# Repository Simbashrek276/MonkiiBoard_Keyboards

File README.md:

# MonkiiBoard Keyboards

Hi! This is the home for the MonkiiBoard keyboards, an open little family of boards you can build, flash and print yourself. There are five of them so far, and each one lives in its own folder with the Arduino code, a 3D printable case and a readme that walks you through it. Remember, for every build (aside from MonkiiPad16 and MonkiiBoard58), there will be 2 build pathways you can take, which are either handwiring or PCB-based builds. For starters, I would recommend choosing the handwiring option for certain keyboard builds, as it would make it much more easier to debug and fix using a multimeter and other tools as well!

## The boards

### MonkiiBoard58
MonkiiBoard58 is the newest and the most ambitious build here! This board packed fifty eight keys in a five by twelve ortholinear grid with a rotary encoder on the left, a ESP23 S3 WROOM U1 (Surface mounted component, not through hole) and no cable to the host at all since it runs wireless off a LiPo battery over Bluetooth (well of course we still have to charge the battery by pluggin the USB_C Receptacle in).

Up to this point, this board only exists as a PCB, no hand wired version, since it carries its own LiPo charger, voltage regulator and a MOSFET power gate for the OLED right alongside the switch matrix. The schematic and layout are finished and the gerbers are ready, but the boards have not gone off to a manufacturer yet, so this is the one board here that has not actually been built in real life.

### MonkiiBoard39
MonkiiBoard39 is MonkiiBoard's second build. THis keyboard has thirty nine keys in a tidy ortholinear 40 percent layout, with sticky modifiers on the bottom row and a Windows key that pops the start menu on a double tap.

MonkiiBoard39 has a PCB now too, no diodes on this one since the sticky modifiers never need more than one key held down at a time. The schematic below shows all thirty nine switches wired straight into the matrix, with the Pro Micro footprint sitting right in the middle of the board.

### MonkiiPad20
MonkiiPad20 is our first keyboard with a OLED screen implemented. This macropad is a a twenty key macropad with an OLED screen, two switchable layers and a set of animated robot eyes that appear when you stop using it for a while (approximately 6 - 8 seconds). It is also the only board here that uses diodes (so far).

For the MonkiiPad20, we've also made our earliest PCB version 1 for this very macropad (if you choose to go the PCB path instead of the handwiring path)! The image below taken is the PCB, where you can see a silkscreen of our logo, MonkiiBoard, on the front layer.

### MonkiiBoard3x3
MonkiiPad3x3 is the first keyboard that we made!! It's a nine key pad that works as a plain number pad until you hold one key (the key "1") to flip it into a macro mode full of arrows and editing shortcuts.

MonkiiPad3x3 got the same treatment, a little PCB with all nine switches and the Pro Micro packed onto one small board, diode free just like MonkiiBoard39.

### MonkiiPad16
MonkiiPad16 is our upgraded macropad, with a knob! This macropad has 16 keys and a rotary encoder, so instead of a second board or a held down FN key you just SPIN the knob to pick a layer, a numpad by default and a page of editing shortcuts one turn away.

## What is in each folder

Every folder is laid out the same way. There is a firmware folder with the Arduino sketch you flash onto the board, a case folder with the print ready STL plates you can drop straight into a slicer, and a readme that covers the wiring, the layout and whatever that particular board likes to do. MonkiiBoard58 is the exception for now, since it has not been built yet its folder only holds the PCB.

## Hand wired or PCB

We designed every board here except MonkiiPad16 and MonkiiBoard58 to be built either hand wired or on its PCB, same firmware and the same layout either way. Hand wiring asks a bit more of you on the materials side, thin gauge wire to run the rows and columns, insulating tape to keep the joints from touching each other, and a steadier hand while you solder everything point to point. The PCB skips all of that since the rows and columns are already routed for you, so it comes down to seating the parts and soldering them to the footprint.

| Needed for | Hand wired | PCB |
| --- | --- | --- |
| Soldering station | Yes | Yes |
| Multimeter | Yes | Yes |
| Solder | Yes | Yes |
| Switches | Yes | Yes |
| Controller board | Yes | Yes |
| Thin wire | Yes | No |
| Insulating tape | Yes | No |
| The PCB itself | No | Yes |

MonkiiPad20 and MonkiiBoard58 are the only boards that need diodes, both 1N4148s, one for every switch. MonkiiBoard39 and MonkiiPad3x3 skip them completely on both their hand wired and PCB builds, and we code the MCUs to enable toggling keys for combinations like Ctrl+C and Ctrl+V instead of holding Ctrl and then press the other button.

## A word on diodes

MonkiiPad20 and MonkiiBoard58 both have a diode sitting under each switch, which is what gives them a clean matrix and proper rollover. The other two boards skip the diodes to keep the build simple and cheap, so they are at their happiest when you press one or two keys at a time. Worth knowing before you start soldering, or before you order parts if MonkiiBoard58 is the one you are building.

## The PCBs at a glance

Four of the five boards now have a PCB option, all designed in KiCad as two layer boards. Here is how they compare.

| Board | Keys | Matrix | Diodes | Controller | Board size |
| --- | --- | --- | --- | --- | --- |
| MonkiiBoard39 | 39 | 4 by 10 | No | Pro Micro (ATmega32U4) | 195 by 80 mm |
| MonkiiPad20 | 20 | 4 by 6 | Yes | RP2040-Zero | 120 by 86 mm |
| MonkiiPad3x3 | 9 | 3 by 3 | No | Pro Micro (ATmega32U4) | 57 by 57 mm |
| MonkiiBoard58 | 58 | 5 by 12 | Yes | ESP32-S3-WROOM-1 N16R8 | 235.45 by 122.95 mm |

MonkiiBoard58 is also the only one of the four running wireless, with its own LiPo charging and voltage regulation on board, and the only one still waiting to actually be manufactured.

Each PCB folder has the full design story, the schematic, the gerbers to get one made, and the raw KiCad project if you want to tune or reroute your own version.

## Getting started

Pick the board you want, open its folder and read through its readme. Wire the matrix to match the pins listed there, flash the sketch from the Arduino IDE, print the plates from the case folder, and you have yourself a keyboard.

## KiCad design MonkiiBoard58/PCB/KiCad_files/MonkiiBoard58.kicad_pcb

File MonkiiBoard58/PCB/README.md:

# MonkiiBoard58 PCB

MonkiiBoard58 is the first board in the family that only exists as a PCB. There is no hand wired version of this one. Fifty eight switches, a rotary encoder and an OLED screen all packed onto one board, running wireless off a LiPo battery instead of a USB cable to the host.

## The layout

Fifty eight keys sit in a five row by twelve column ortholinear grid, sixty switch positions in total with two given up in the middle for the OLED window. An EC11 rotary encoder lives on the left side and a USB C receptacle sits in the top right corner for charging.

## How I designed it

I drew the matrix first, fifty eight switches each with their own 1N4148 diode, then moved on to the ESP32 S3 module, the OLED header, the encoder and the whole power section afterward.

The power side got its own sheet since there was too much going on to squeeze in next to the matrix. Battery connector, power switch, the AMS1117 regulator and its capacitors all sit together here.

## Laying it out

The first pass at routing did not have a single mounting hole anywhere on the board, which would have left no way to actually screw it into a case later. Version two added four of them, one in each corner.

## Placing and wiring the parts

Before anything got soldered I laid every part out on the bench to check the footprints against the real components first.

## The power system

This is the part that sets MonkiiBoard58 apart from the rest of the family. USB C brings in five volts, the TP4056 uses that to charge the LiPo battery, and everything downstream of the power switch runs off the AMS1117 regulator at a steady 3.3 volts.

| Stage | Part | Job |
| --- | --- | --- |
| Charging | TP4056 | Charges the LiPo off USB C, current set by a 1.2 kilo ohm PROG resistor, up to one amp |
| Regulation | AMS1117 3.3 | Takes the battery voltage and holds a steady 3.3 volt rail for everything else |
| OLED gating | AO3401A | P channel MOSFET that cuts power to the OLED completely when the ESP32 S3 pulls the gate high |
| Battery sensing | Resistor divider | 1 megaohm and 806 kiloohm divider scaling the 4.2 volt max battery voltage down into the ADC range |

The OLED gate is the part I am proudest of. Instead of just dimming the screen in software, the ESP32 S3 can cut its power rail entirely after thirty seconds of no key presses, so there is zero standby draw from the display while the board sits idle.

## The switches

All fifty eight switches sit in a five row by twelve column matrix, and unlike MonkiiBoard39 or MonkiiPad3x3 this one does use a diode per switch, a 1N4148 with the cathode facing the row line. With sixty positions on a wireless board meant for real typing, full rollover mattered enough to spend the extra part on every switch.

## The pinout

| Function | ESP32 S3 GPIO |
| --- | --- |
| Row 0 | GPIO4 |
| Row 1 | GPIO5 |
| Row 2 | GPIO6 |
| Row 3 | GPIO7 |
| Row 4 | GPIO8 |
| Col 0 | GPIO9 |
| Col 1 | GPIO10 |
| Col 2 | GPIO11 |
| Col 3 | GPIO12 |
| Col 4 | GPIO13 |
| Col 5 | GPIO14 |
| Col 6 | GPIO15 |
| Col 7 | GPIO16 |
| Col 8 | GPIO17 |
| Col 9 | GPIO18 |
| Col 10 | GPIO21 |
| Col 11 | GPIO38 |
| OLED SDA | GPIO1 |
| OLED SCL | GPIO2 |
| OLED power gate | GPIO39 |
| Encoder A | GPIO40 |
| Encoder B | GPIO41 |
| Encoder switch | GPIO42 |
| Battery ADC | GPIO3 |

## The controller

An ESP32 S3 WROOM 1 N16R8 sits at the top center of the board, antenna facing out toward the edge with a keep out zone underneath it so nothing on any layer sits under or around the antenna. The S3 has a native USB PHY, so the USB C lines wire straight into it with no separate USB to serial chip needed, and it talks Bluetooth 5 for the wireless side once the firmware is flashed.

## What the board is

| Spec | Value |
| --- | --- |
| Layers | 2 |
| Thickness | 1.6 mm |
| Size | 235.45 by 122.95 mm |
| Finish | None |

## Downloading the files

`MonkiiBoard58_PCB.zip` in this folder has the copper, mask, paste and silkscreen layers for both sides along with the edge cuts and the job file. There is no drill file in there yet, so pull that from the KiCad project in `KiCad_files` and add it before sending this off to a fab house.

## Tuning your own PCB

If you want to design or tune your own version of this board, the raw KiCad project sits in `KiCad_files` right next to the gerbers. Download those three files, open the `.kicad_pro` in KiCad, and you get the schematic and the board exactly as I left them. Edit the schematic, move footprints, reroute traces, whatever your build actually needs, then export your own gerbers when you are happy with it.

## Where things stand right now

This one is still ahead of the rest of the pack in age but behind everyone else in progress. The schematic and layout are done and the gerbers are ready, but I have not sent the boards off to a manufacturer yet, so nothing has actually been built or tested on real hardware. Firmware and a case are next once boards are in hand. Like every other board here it is fully open source, so the KiCad project and every file in this folder are free to build, copy or change however you like.

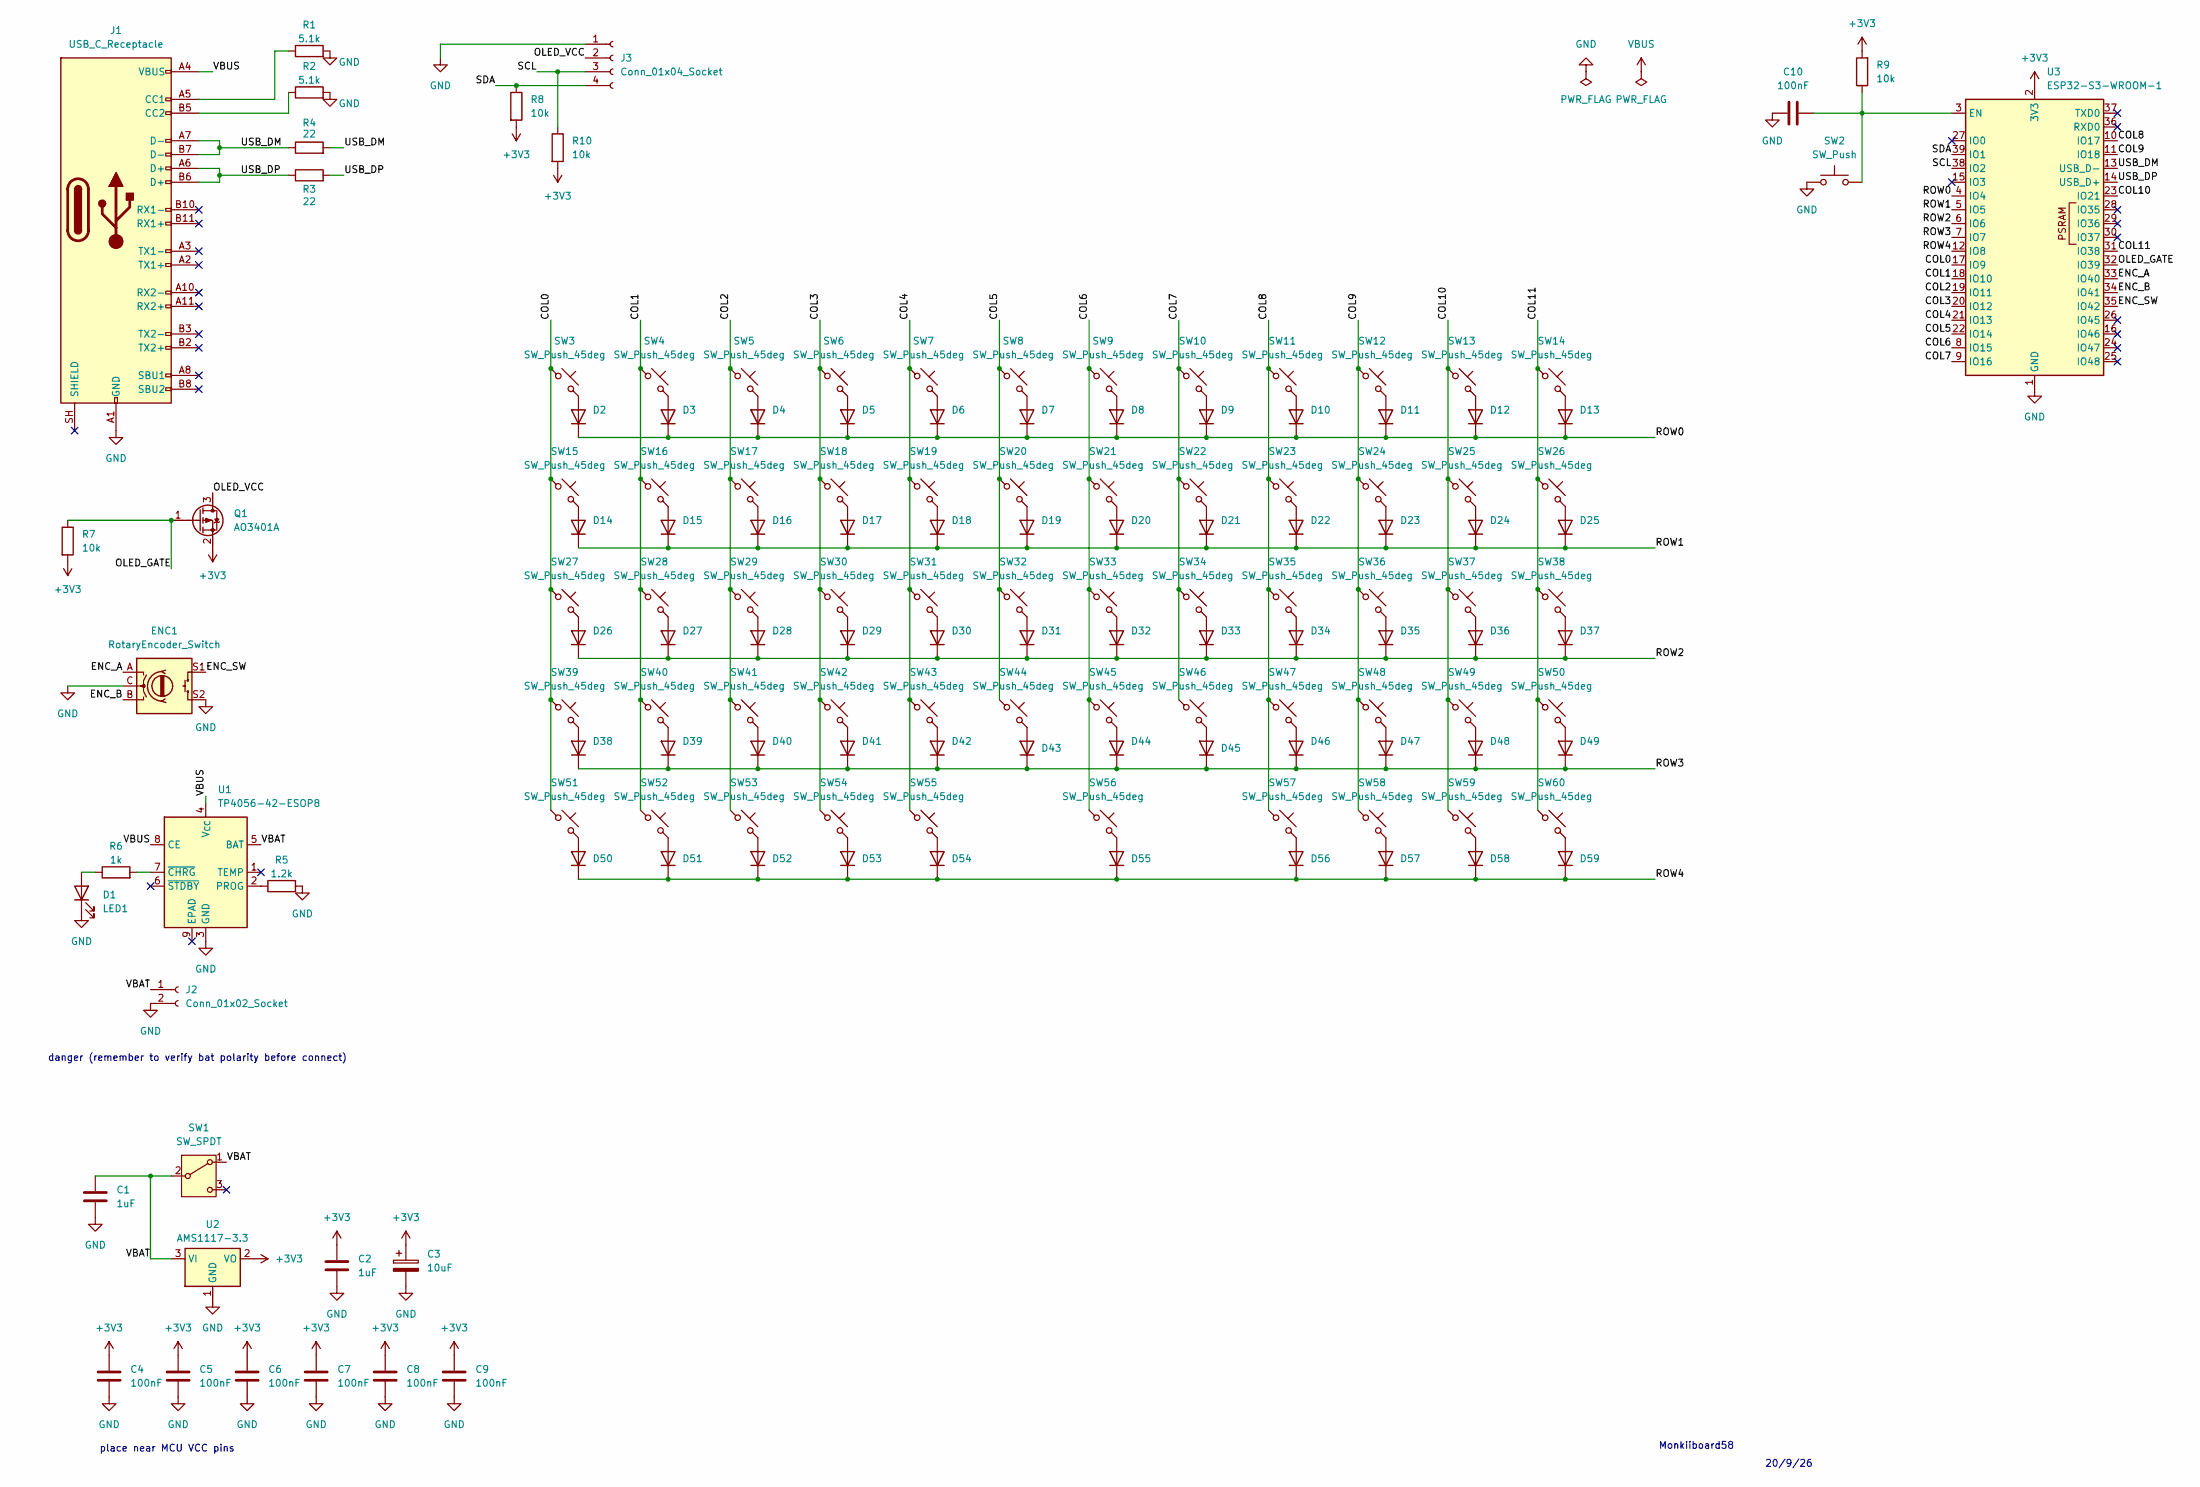
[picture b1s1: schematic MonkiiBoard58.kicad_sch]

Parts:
C1, C2: 1uF; C_0402_1005Metric
C3: 10uF; C_0402_1005Metric
C4, C5, C6, C7, C8, C9, C10: 100nF; C_0402_1005Metric
D1: LED1; LED_0603_1608Metric
D2, D3, D4, D5, D6, D7, D8, D9, D10, D11, D12, D13, D14, D15, D16, D17, D18, D19, D20, D21, D22, D23, D24, D25, D26, D27, D28, D29, D30, D31, D32, D33, D34, D35, D36, D37, D38, D39, D40, D41, D42, D43, D44, D45, D46, D47, D48, D49, D50, D51, D52, D53, D54, D55, D56, D57, D58, D59: 1N4148; D_DO-35_SOD27_P7.62mm_Horizontal
ENC1: RotaryEncoder_Switch; RotaryEncoder_Alps_EC11E-Switch_Vertical_H20mm
J1: USB_C_Receptacle; USB_C_Receptacle_GCT_USB4085
J2: Conn_01x02_Socket; JST_PH_B2B-PH-K_1x02_P2.00mm_Vertical
J3: Conn_01x04_Socket; PinSocket_1x04_P2.54mm_Vertical
Q1: AO3401A; SOT-23
R1, R2: 5.1k; R_0402_1005Metric
R3, R4: 22; R_0402_1005Metric
R5: 1.2k; R_0402_1005Metric
R6: 1k; R_0402_1005Metric
R7, R8, R9, R10: 10k; R_0402_1005Metric
SW1: SW_SPDT; SW_SPDT_PCM12
SW2: SW_Push; SW_SPST_B3U-1000P
SW3, SW4, SW5, SW6, SW7, SW8, SW9, SW10, SW11, SW12, SW13, SW14, SW15, SW16, SW17, SW18, SW19, SW20, SW21, SW22, SW23, SW24, SW25, SW26, SW27, SW28, SW29, SW30, SW31, SW32, SW33, SW34, SW35, SW36, SW37, SW38, SW39, SW40, SW41, SW42, SW43, SW44, SW45, SW46, SW47, SW48, SW49, SW50, SW51, SW52, SW53, SW54, SW57, SW58, SW59, SW60: SW_Push_45deg; SW_Cherry_MX_1.00u_PCB
SW55, SW56: SW_Push_45deg; SW_Cherry_MX_2.00u_PCB
U1: TP4056-42-ESOP8; SOIC-8-1EP_3.9x4.9mm_P1.27mm_EP2.41x3.3mm_ThermalVias
U2: AMS1117-3.3; SOT-223-3_TabPin2
U3: ESP32-S3-WROOM-1

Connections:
+3V3: C2.1, C3.1, C4.1, C5.1, C6.1, C7.1, C8.1, C9.1, Q1.2 (S), R7.2, R8.2, R9.2, R10.2, U2.2 (VO), U3.2 (3V3)
/COL0: SW3.1, SW15.1, SW27.1, SW39.1, SW51.1, U3.17 (IO9)
/COL1: SW4.1, SW16.1, SW28.1, SW40.1, SW52.1, U3.18 (IO10)
/COL2: SW5.1, SW17.1, SW29.1, SW41.1, SW53.1, U3.19 (IO11)
/COL3: SW6.1, SW18.1, SW30.1, SW42.1, SW54.1, U3.20 (IO12)
/COL4: SW7.1, SW19.1, SW31.1, SW43.1, SW55.1, U3.21 (IO13)
/COL5: SW8.1, SW20.1, SW32.1, SW44.1, U3.22 (IO14)
/COL6: SW9.1, SW21.1, SW33.1, SW45.1, SW56.1, U3.8 (IO15)
/COL7: SW10.1, SW22.1, SW34.1, SW46.1, U3.9 (IO16)
/COL8: SW11.1, SW23.1, SW35.1, SW47.1, SW57.1, U3.10 (IO17)
/COL9: SW12.1, SW24.1, SW36.1, SW48.1, SW58.1, U3.11 (IO18)
/COL10: SW13.1, SW25.1, SW37.1, SW49.1, SW59.1, U3.23 (IO21)
/COL11: SW14.1, SW26.1, SW38.1, SW50.1, SW60.1, U3.31 (IO38)
/ENC_A: ENC1.A, U3.33 (IO40)
/ENC_B: ENC1.B, U3.34 (IO41)
/ENC_SW: ENC1.S1, U3.35 (IO42)
/OLED_GATE: Q1.1 (G), R7.1, U3.32 (IO39)
/OLED_VCC: J3.2, Q1.3 (D)
/ROW0: D2.1 (K), D3.1 (K), D4.1 (K), D5.1 (K), D6.1 (K), D7.1 (K), D8.1 (K), D9.1 (K), D10.1 (K), D11.1 (K), D12.1 (K), D13.1 (K), U3.4 (IO4)
/ROW1: D14.1 (K), D15.1 (K), D16.1 (K), D17.1 (K), D18.1 (K), D19.1 (K), D20.1 (K), D21.1 (K), D22.1 (K), D23.1 (K), D24.1 (K), D25.1 (K), U3.5 (IO5)
/ROW2: D26.1 (K), D27.1 (K), D28.1 (K), D29.1 (K), D30.1 (K), D31.1 (K), D32.1 (K), D33.1 (K), D34.1 (K), D35.1 (K), D36.1 (K), D37.1 (K), U3.6 (IO6)
/ROW3: D38.1 (K), D39.1 (K), D40.1 (K), D41.1 (K), D42.1 (K), D43.1 (K), D44.1 (K), D45.1 (K), D46.1 (K), D47.1 (K), D48.1 (K), D49.1 (K), U3.7 (IO7)
/ROW4: D50.1 (K), D51.1 (K), D52.1 (K), D53.1 (K), D54.1 (K), D55.1 (K), D56.1 (K), D57.1 (K), D58.1 (K), D59.1 (K), U3.12 (IO8)
/SCL: J3.3, R10.1, U3.38 (IO2)
/SDA: J3.4, R8.1, U3.39 (IO1)
/USB_DM: J1.A7 (D-), J1.B7 (D-), R4.1, R4.2, U3.13 (USB_D-)
/USB_DP: J1.A6 (D+), J1.B6 (D+), R3.1, R3.2, U3.14 (USB_D+)
/VBAT: C1.1, J2.1, SW1.1 (A), SW1.2 (B), U1.5 (BAT), U2.3 (VI)
GND: C1.2, C2.2, C3.2, C4.2, C5.2, C6.2, C7.2, C8.2, C9.2, C10.1, D1.1 (K), ENC1.C, ENC1.S2, J1.A1 (GND), J1.A12 (GND), J1.B1 (GND), J1.B12 (GND), J2.2, J3.1, R1.2, R2.2, R5.2, SW2.1, U1.3 (GND), U2.1 (GND), U3.1 (GND), U3.40 (GND), U3.41 (GND)
unnamed: D1.2 (A), R6.1
unnamed: D2.2 (A), SW3.2
unnamed: D3.2 (A), SW4.2
unnamed: D4.2 (A), SW5.2
unnamed: D5.2 (A), SW6.2
unnamed: D6.2 (A), SW7.2
unnamed: D7.2 (A), SW8.2
unnamed: D8.2 (A), SW9.2
unnamed: D9.2 (A), SW10.2
unnamed: D10.2 (A), SW11.2
unnamed: D11.2 (A), SW12.2
unnamed: D12.2 (A), SW13.2
unnamed: D13.2 (A), SW14.2
unnamed: D14.2 (A), SW15.2
unnamed: D15.2 (A), SW16.2
unnamed: D16.2 (A), SW17.2
unnamed: D17.2 (A), SW18.2
unnamed: D18.2 (A), SW19.2
unnamed: D19.2 (A), SW20.2
unnamed: D20.2 (A), SW21.2
unnamed: D21.2 (A), SW22.2
unnamed: D22.2 (A), SW23.2
unnamed: D23.2 (A), SW24.2
unnamed: D24.2 (A), SW25.2
unnamed: D25.2 (A), SW26.2
unnamed: D26.2 (A), SW27.2
unnamed: D27.2 (A), SW28.2
unnamed: D28.2 (A), SW29.2
unnamed: D29.2 (A), SW30.2
unnamed: D30.2 (A), SW31.2
unnamed: D31.2 (A), SW32.2
unnamed: D32.2 (A), SW33.2
unnamed: D33.2 (A), SW34.2
unnamed: D34.2 (A), SW35.2
unnamed: D35.2 (A), SW36.2
unnamed: D36.2 (A), SW37.2
unnamed: D37.2 (A), SW38.2
unnamed: D38.2 (A), SW39.2
unnamed: D39.2 (A), SW40.2
unnamed: D40.2 (A), SW41.2
unnamed: D41.2 (A), SW42.2
unnamed: D42.2 (A), SW43.2
unnamed: D43.2 (A), SW44.2
unnamed: D44.2 (A), SW45.2
unnamed: D45.2 (A), SW46.2
unnamed: D46.2 (A), SW47.2
unnamed: D47.2 (A), SW48.2
unnamed: D48.2 (A), SW49.2
unnamed: D49.2 (A), SW50.2
unnamed: D50.2 (A), SW51.2
unnamed: D51.2 (A), SW52.2
unnamed: D52.2 (A), SW53.2
unnamed: D53.2 (A), SW54.2
unnamed: D54.2 (A), SW55.2
unnamed: D55.2 (A), SW56.2
unnamed: D56.2 (A), SW57.2
unnamed: D57.2 (A), SW58.2
unnamed: D58.2 (A), SW59.2
unnamed: D59.2 (A), SW60.2
unnamed: J1.A5 (CC1), R1.1
unnamed: J1.B5 (CC2), R2.1
unnamed: R5.1, U1.2 (PROG)
unnamed: R6.2, U1.7 (~CHRG)
unnamed: C10.2, R9.1, SW2.2, U3.3 (EN)
VBUS: J1.A4 (VBUS), J1.A9 (VBUS), J1.B4 (VBUS), J1.B9 (VBUS), U1.4 (V_{CC}), U1.8 (CE)

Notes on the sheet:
Monkiiboard58
danger (remember to verify bat polarity before connect)
place near MCU VCC pins
20/9/26

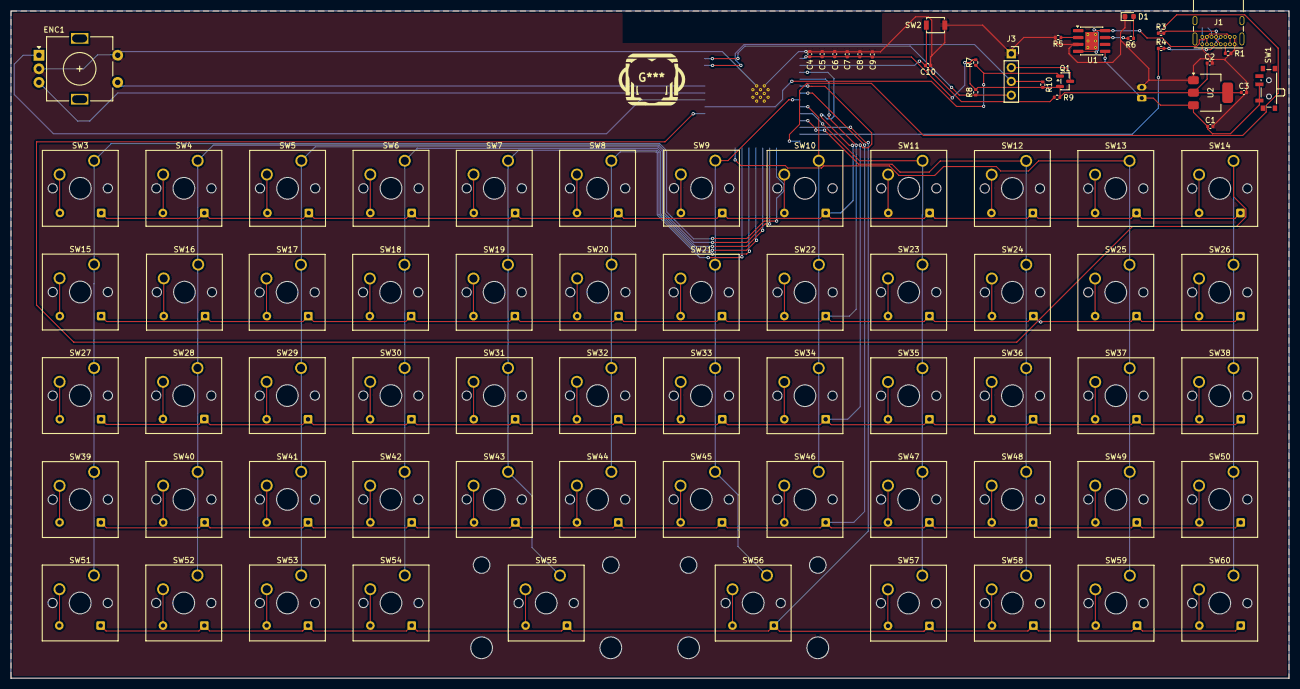
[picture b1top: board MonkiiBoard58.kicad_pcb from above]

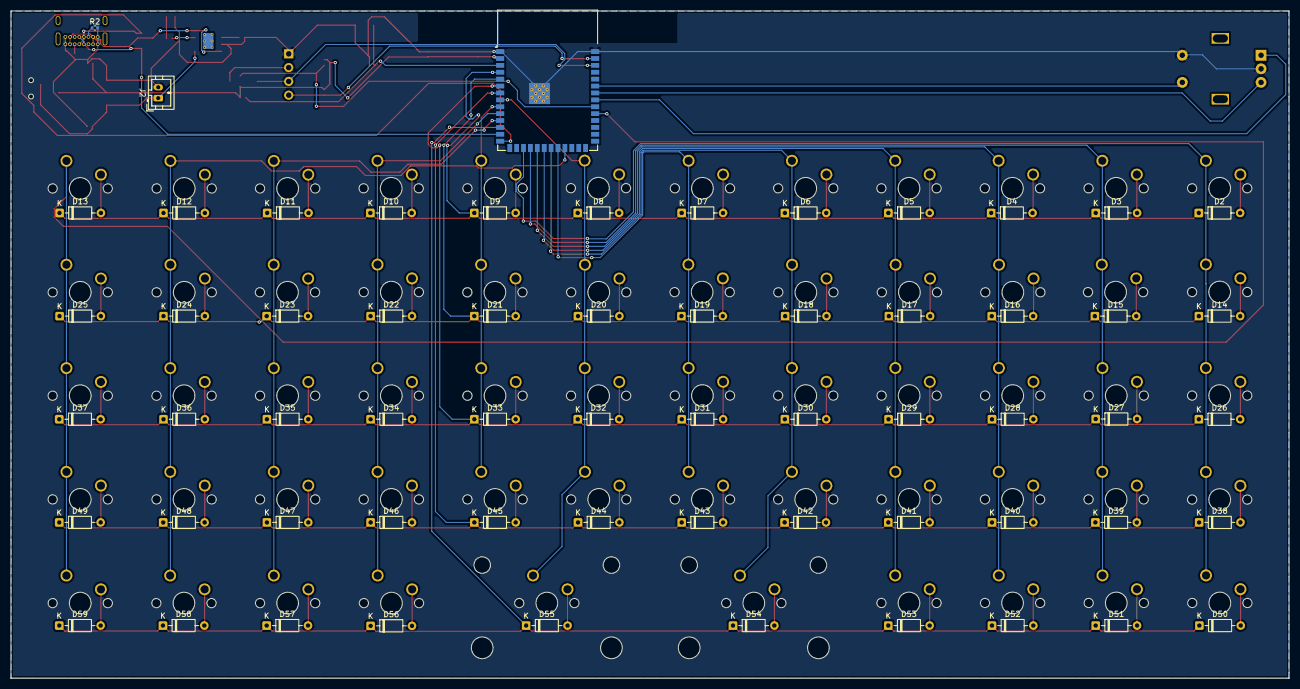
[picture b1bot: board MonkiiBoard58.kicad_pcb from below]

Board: 2 copper layers, 235.4 x 122.9 mm, 147 parts (61 on the bottom side), 94 nets.

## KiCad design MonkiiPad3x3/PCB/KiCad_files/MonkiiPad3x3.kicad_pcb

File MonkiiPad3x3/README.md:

# MonkiiPad3x3

The smallest board in the family, a nine key pad in a simple three by three grid. It is a Pro Micro style board that turns up as an ordinary keyboard, and despite its size it hides a whole second personality behind a long press.

## How it is wired

Nine switches sit in a grid of three rows and three columns. The rows go to pins 2, 3 and 4, and the columns go to pins 5, 6 and 7. Like the MonkiiBoard39 it runs without diodes, so it is built for tapping one key at a time rather than holding a fistful of them down together, which suits a little number pad just fine.

## Two ways to build it

You can hand wire it to the pins above like the original, or order the PCB I designed and solder onto that instead. Same firmware, same pins, no diodes either way.

The design story and the files to get one made live in the [PCB folder](PCB/).

## Two pads in one

Fresh out of the box the pad is a number pad. The nine keys send 1 through 9 laid out exactly how you would picture them, top left down to bottom right.

The top left key is the one to watch. A quick tap sends a 1 like any other key. Hold it down for a second and a half though, and the pad flips into macro mode, and holding it again flips you straight back. It is a neat way to pack twice the function into nine keys without adding a single extra button.

## Macro mode

Once you are in macro mode the layout turns into an editing and navigation cluster. The four keys around the middle become arrow keys, laid out as a cross, with up on the top key and left, down and right across the middle row.

The bottom row becomes editing commands. The bottom left key fires undo, the middle one fires redo, and the bottom right sends delete.

One quick heads up if you go reading the code. The little comments next to those two bottom keys say copy and paste, but what the keys actually send is undo, as control and z, and redo, as control and y. The behavior is the undo and redo pair, the comments just did not keep up with the code.

## The case

The case folder holds the print ready plates for the pad, filed under the VOID9 name. There are a few flavours to pick from. The top comes in a plain flat version and a softer filleted version, and the bottom comes flat or gently angled if you like the pad to sit on a slight tilt. Print whichever top and bottom pair you fancy, then clip the switches into place.

## Flashing it

Open the sketch in the Arduino IDE, choose the Arduino Leonardo or SparkFun Pro Micro board and upload. It only uses the built in Keyboard library, so there is nothing else to install.

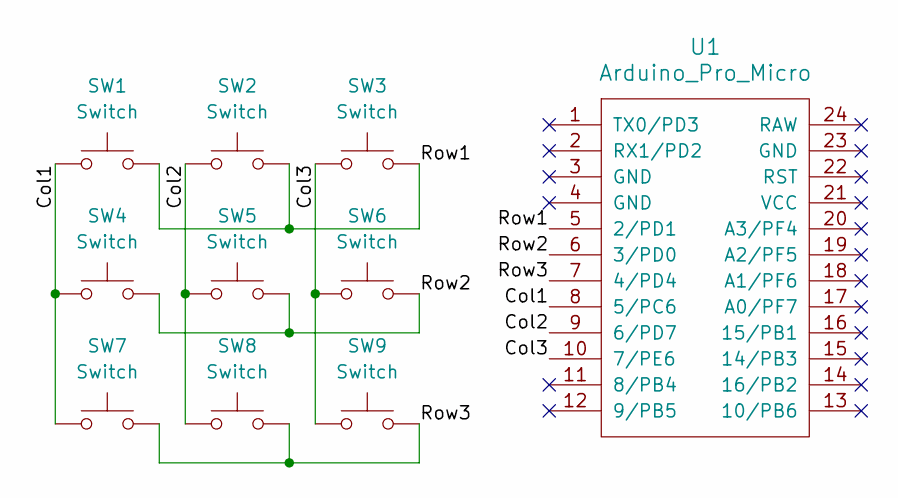
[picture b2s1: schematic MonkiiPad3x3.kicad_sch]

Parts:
SW1, SW2, SW3, SW4, SW5, SW6, SW7, SW8, SW9: Switch; SW_Cherry_MX_1.00u_PCB
U1: Arduino_Pro_Micro

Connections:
/Col1: SW1.1, SW4.1, SW7.1, U1.8 (5/PC6)
/Col2: SW2.1, SW5.1, SW8.1, U1.9 (6/PD7)
/Col3: SW3.1, SW6.1, SW9.1, U1.10 (7/PE6)
/Row1: SW1.2, SW2.2, SW3.2, U1.5 (2/PD1)
/Row2: SW4.2, SW5.2, SW6.2, U1.6 (3/PD0)
/Row3: SW7.2, SW8.2, SW9.2, U1.7 (4/PD4)

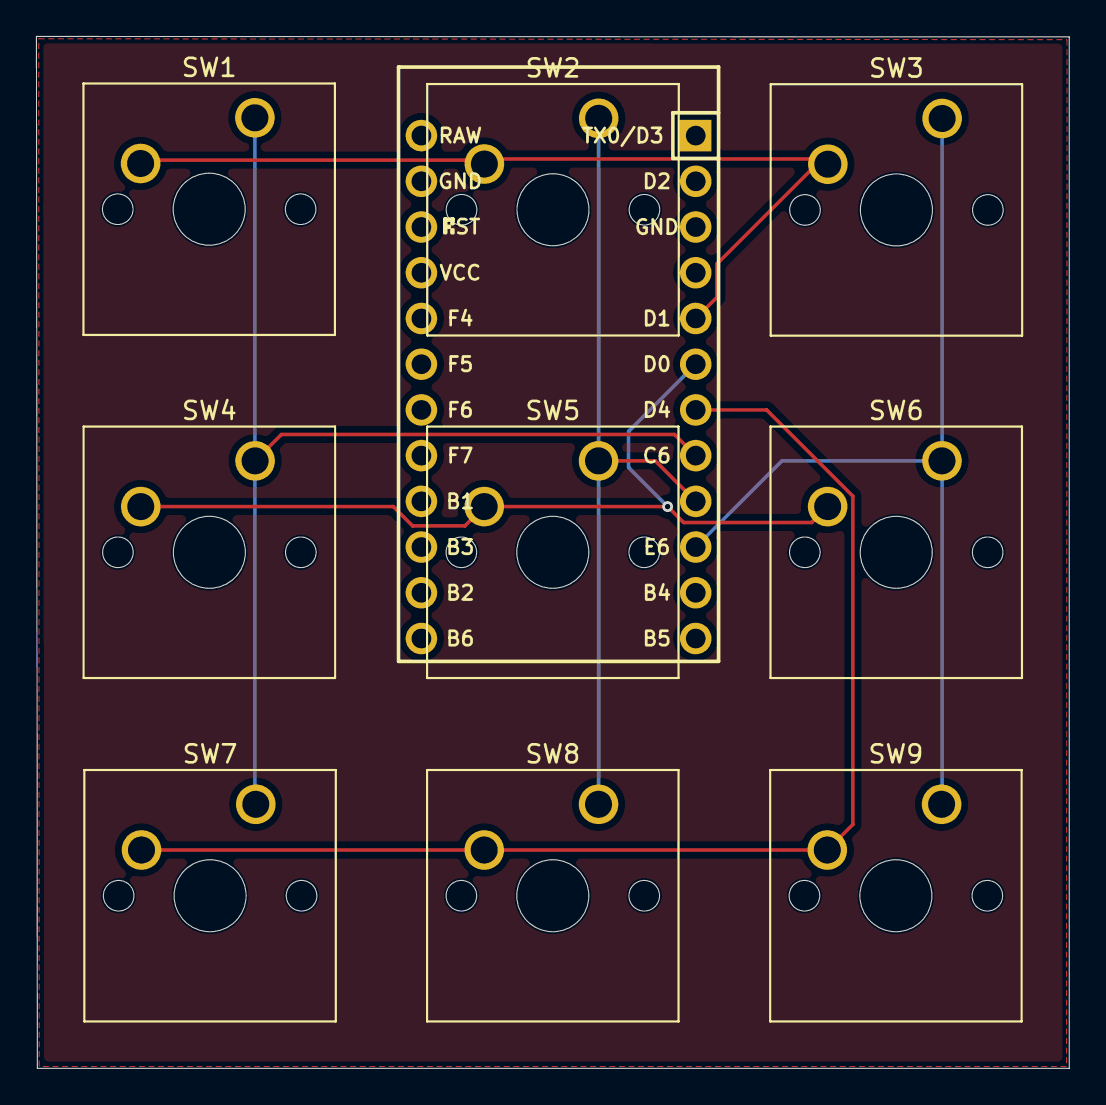
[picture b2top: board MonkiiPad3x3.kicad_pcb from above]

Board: 2 copper layers, 57.4 x 57.3 mm, 10 parts (1 on the bottom side), 6 nets.

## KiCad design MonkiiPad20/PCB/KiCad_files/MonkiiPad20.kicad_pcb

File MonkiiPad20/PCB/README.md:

# MonkiiPad20 PCB

This is the circuit board I designed for the MonkiiPad20. It turns the pile of switches, diodes and a controller into one tidy piece instead of a nest of hand wiring. Twenty switch spots, a diode under each one, an RP2040 footprint in the corner and a little header for the OLED, all on a two layer board.

## Downloading the files

If you just want to get this board made, **grab `MonkiiPad20_PCB.zip`**. That one zip holds everything a fab house needs, all the Gerber layers plus the two drill files, and most manufacturers want it handed over exactly like that, as a single archive. Drop the zip into their site, pick your options and you are done.

The loose `.gbr` and `.drl` files sitting next to the zip are the same data unpacked. They are there if you want to peek at a layer or load it into a Gerber viewer, but for ordering you only need the zip.

## What the board is

It came out of KiCad as a two layer board, 120 by 86 millimetres, 1.6 mm thick, with green soldermask. Nothing exotic in there, so any of the usual cheap fab houses will run it without complaint.

## The switches and diodes

The twenty switch positions are laid out four rows by six columns and numbered SW1 through SW20 on the silkscreen, so you always know which one you are looking at. Every switch gets its own diode, and the footprint sits right beside it with the cathode end marked K. That little mark matters, since diodes only go one way, so line the band on the diode up with the K and you will not have to desolder anything later. The diodes are what give the pad its clean matrix and let you mash several keys at once without ghosting.

## The controller

Up in the corner is the footprint for the Waveshare RP2040-Zero. I printed the pin names right onto the silkscreen, the power pins down one side as 5V, GND and 3V3, and the GPIO numbers running around the rest, so you can seat the controller and check your wiring against the board itself instead of digging out a pinout. There is also a small header broken out for the OLED so the screen has a clean place to land.

## Getting it made

Send the zip to whichever fab you like, the defaults are fine, two layers and 1.6 mm as above. When the boards land, solder the diodes first while the board is still flat and easy to work on, watching that K mark, then the switches, then the controller and the OLED header. After that you are ready to flash the firmware and drop it into the case.

## What it looks like built

Here is one I actually populated, every switch socketed and the OLED window sitting flush in the corner.

A closer look at the diodes once they are actually soldered down instead of just sitting as a footprint. Every one bent flat and facing the same way, matching the K printed beside it.

The RP2040-Zero seated on its header, its own silkscreened pin labels lining up right against the ones printed on the board underneath.

And the whole back once everything is in, controller and every diode soldered.

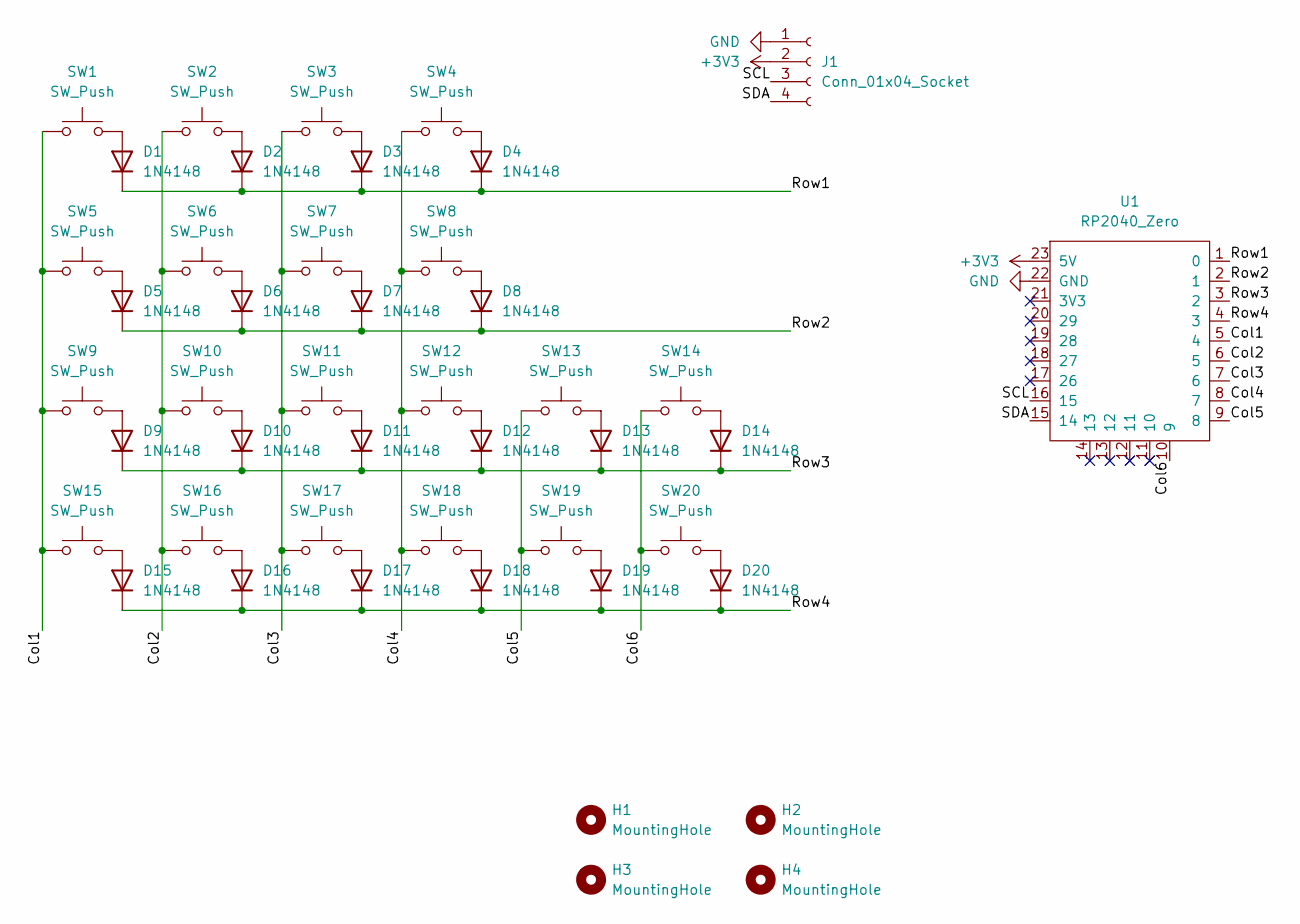
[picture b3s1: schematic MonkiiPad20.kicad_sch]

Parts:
D1, D2, D3, D4, D5, D6, D7, D8, D9, D10, D11, D12, D13, D14, D15, D16, D17, D18, D19, D20: 1N4148; D_DO-35_SOD27_P7.62mm_Horizontal
H1, H2, H3, H4: MountingHole; MountingHole_4mm
J1: Conn_01x04_Socket; PinHeader_1x04_P2.54mm_Vertical
SW1, SW2, SW3, SW4, SW5, SW6, SW7, SW8, SW9, SW10, SW11, SW12, SW13, SW14, SW15, SW16, SW17, SW18, SW19, SW20: SW_Push; SW_Cherry_MX_1.00u_PCB
U1: RP2040_Zero

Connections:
+3V3: J1.2, U1.23 (5V)
/Col1: SW1.1, SW5.1, SW9.1, SW15.1, U1.5 (4)
/Col2: SW2.1, SW6.1, SW10.1, SW16.1, U1.6 (5)
/Col3: SW3.1, SW7.1, SW11.1, SW17.1, U1.7 (6)
/Col4: SW4.1, SW8.1, SW12.1, SW18.1, U1.8 (7)
/Col5: SW13.1, SW19.1, U1.9 (8)
/Col6: SW14.1, SW20.1, U1.10 (9)
/Row1: D1.1 (K), D2.1 (K), D3.1 (K), D4.1 (K), U1.1 (0)
/Row2: D5.1 (K), D6.1 (K), D7.1 (K), D8.1 (K), U1.2 (1)
/Row3: D9.1 (K), D10.1 (K), D11.1 (K), D12.1 (K), D13.1 (K), D14.1 (K), U1.3 (2)
/Row4: D15.1 (K), D16.1 (K), D17.1 (K), D18.1 (K), D19.1 (K), D20.1 (K), U1.4 (3)
/SCL: J1.3, U1.16 (15)
/SDA: J1.4, U1.15 (14)
GND: J1.1, U1.22 (GND)
unnamed: D1.2 (A), SW1.2
unnamed: D2.2 (A), SW2.2
unnamed: D3.2 (A), SW3.2
unnamed: D4.2 (A), SW4.2
unnamed: D5.2 (A), SW5.2
unnamed: D6.2 (A), SW6.2
unnamed: D7.2 (A), SW7.2
unnamed: D8.2 (A), SW8.2
unnamed: D9.2 (A), SW9.2
unnamed: D10.2 (A), SW10.2
unnamed: D11.2 (A), SW11.2
unnamed: D12.2 (A), SW12.2
unnamed: D13.2 (A), SW13.2
unnamed: D14.2 (A), SW14.2
unnamed: D15.2 (A), SW15.2
unnamed: D16.2 (A), SW16.2
unnamed: D17.2 (A), SW17.2
unnamed: D18.2 (A), SW18.2
unnamed: D19.2 (A), SW19.2
unnamed: D20.2 (A), SW20.2

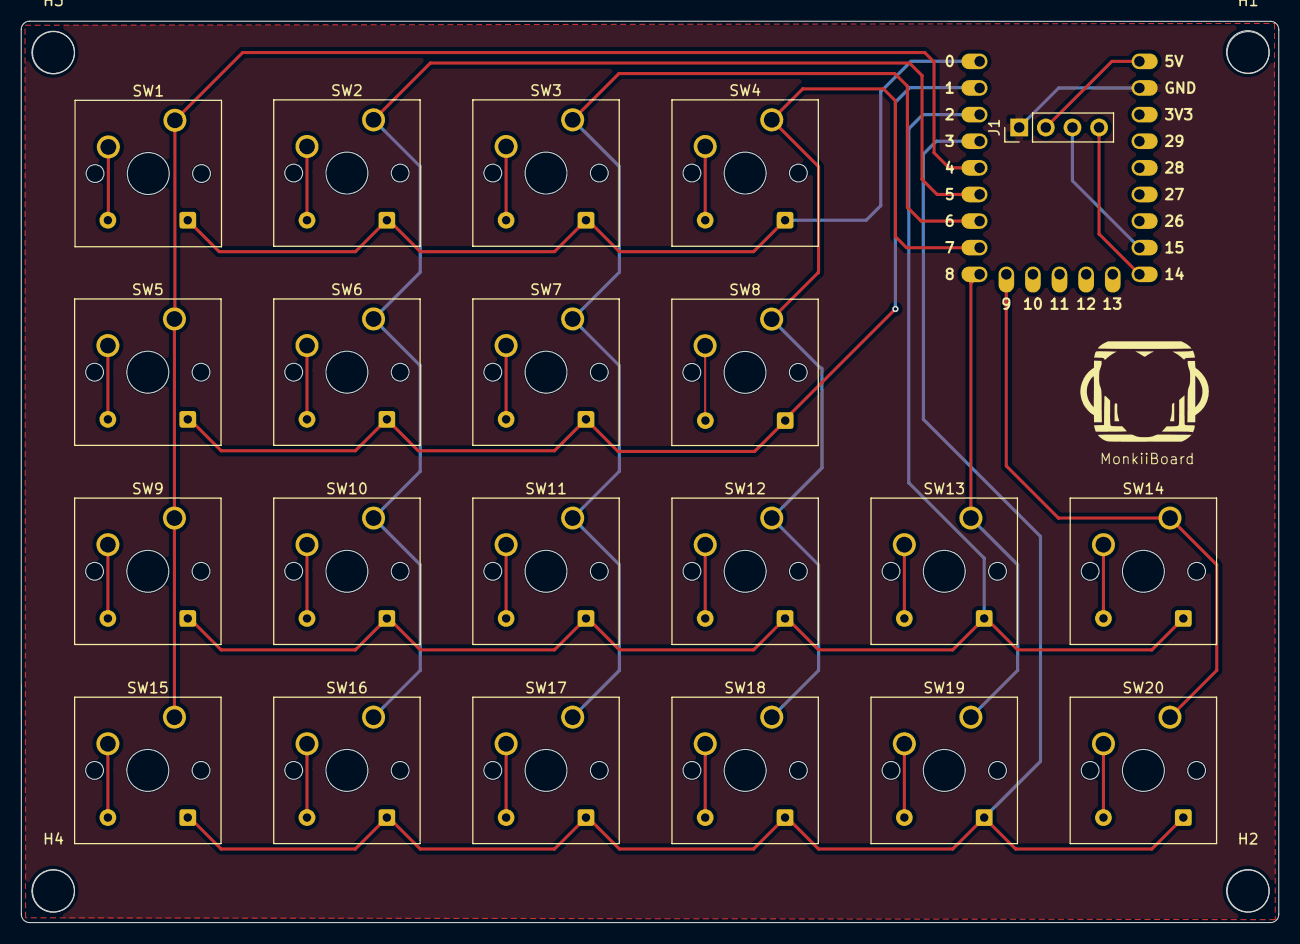
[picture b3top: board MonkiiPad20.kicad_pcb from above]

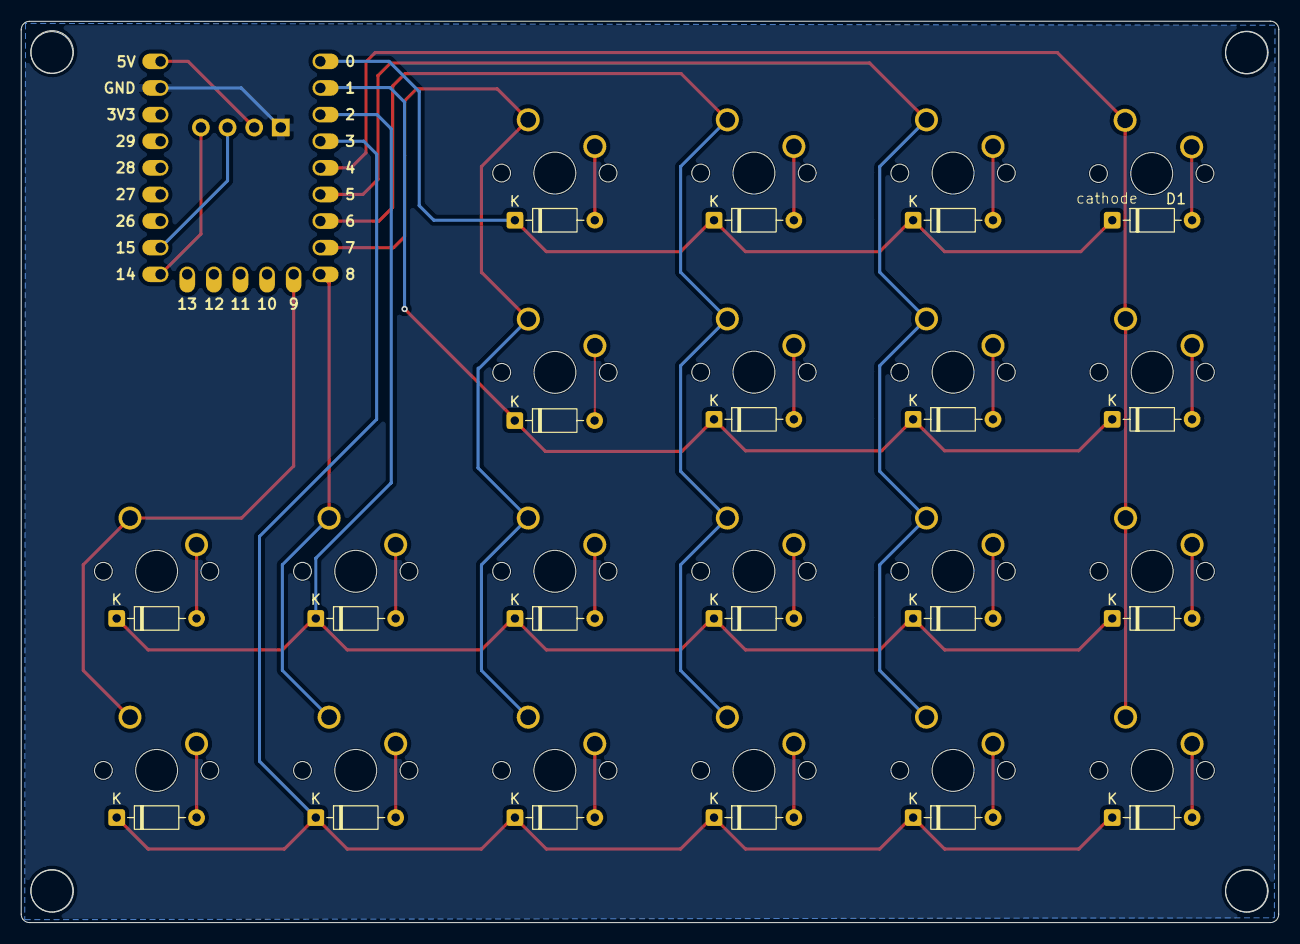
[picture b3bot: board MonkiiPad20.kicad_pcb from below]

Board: 2 copper layers, 120.0 x 86.0 mm, 46 parts (21 on the bottom side), 34 nets.
